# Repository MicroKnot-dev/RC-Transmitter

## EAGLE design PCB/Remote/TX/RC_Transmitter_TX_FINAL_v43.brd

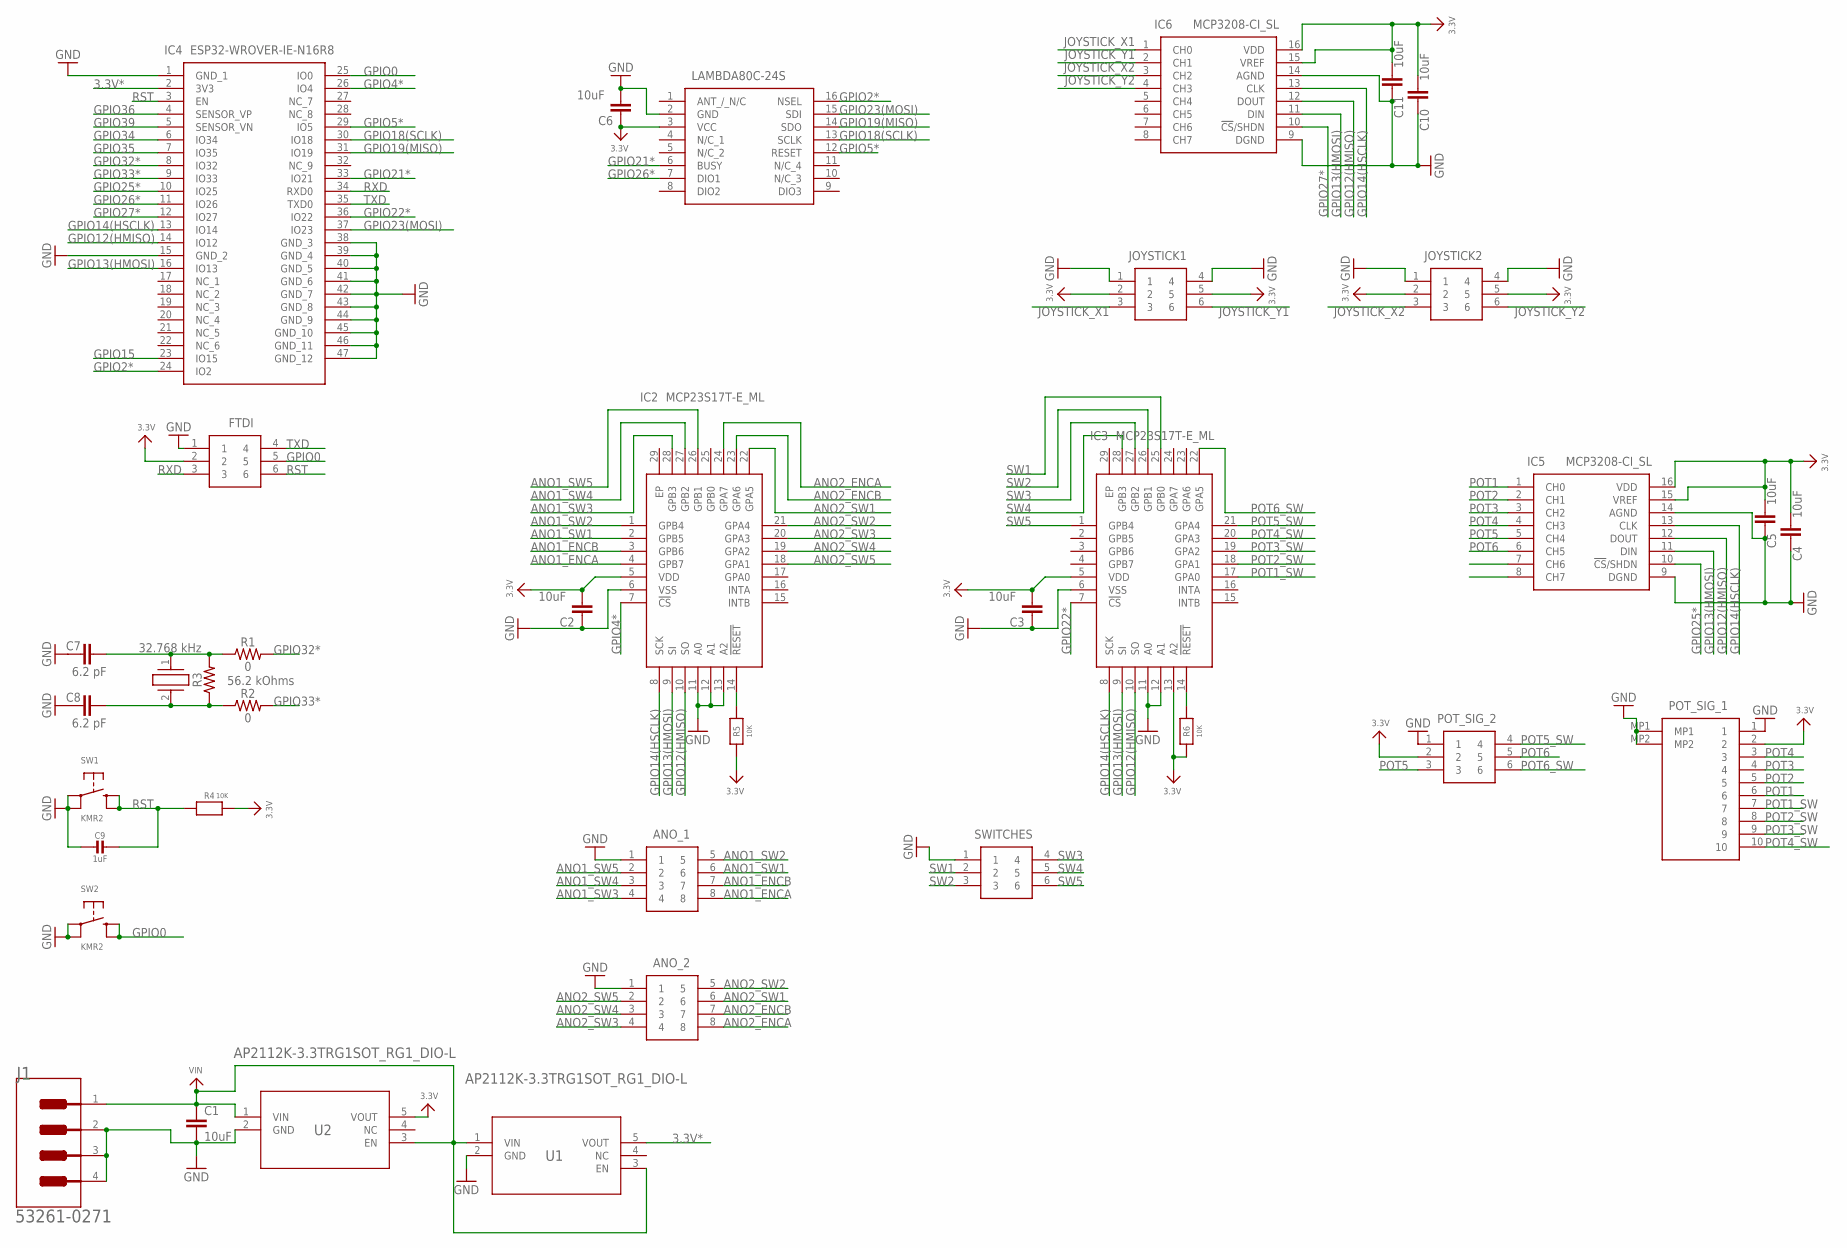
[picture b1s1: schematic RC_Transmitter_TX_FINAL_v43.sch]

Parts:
ANO_1, ANO_2: 0532610871; 53261-0871
C1, C2, C3, C4, C5, C6, C10, C11: 10uF; 0805
C7, C8: 6.2 pF; CAPC2012X110
C9: 1uF; 0805-NO
CRYSTAL: 32.768 kHz; ECX327CDX1293
FTDI: 0532610671
IC1: LAMBDA80C-24S; LAMBDA80C24S
IC2, IC3: MCP23S17T-E_ML; QFN65P600X600X100-29N
IC4: ESP32-WROVER-IE-N16R8; ESP32WROVERIEN16R8
IC5, IC6: MCP3208-CI_SL; SOIC127P600X175-16N
J1: MOLEX_53261-0271MOLEX_53261-0271_0_0; MOLEX_53261-0271_0
JOYSTICK1, JOYSTICK2: 0532610671
POT_SIG_1: 0532611071
POT_SIG_2: 0532610671
R1, R2: 0; 0603
R3: 56.2 kOhms; 0603
R4, R5, R6: 10K; _0805
SW1, SW2: KMR2; BTN_KMR2_4.6X2.8
SWITCHES: 0532610671
U1, U2: AP2112K-3.3TRG1SOT_RG1_DIO-L; SOT_RG1_DIO-L

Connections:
3.3V: C2.2, C3.2, C4.2, C5.2, C6.1, C10.2, C11.2, FTDI.2, IC1.3 (VCC), IC2.5 (VDD), IC3.5 (VDD), IC3.13 (A2), IC5.15 (VREF), IC5.16 (VDD), IC6.15 (VREF), IC6.16 (VDD), JOYSTICK1.2, JOYSTICK1.5, JOYSTICK2.2, JOYSTICK2.5, POT_SIG_1.2, POT_SIG_2.2, R4.2, R5.1, R6.1, U2.5 (VOUT)
3.3V*: IC4.2 (3V3), U1.5 (VOUT)
ANO1_ENCA: ANO_1.8, IC2.4 (GPB7)
ANO1_ENCB: ANO_1.7, IC2.3 (GPB6)
ANO1_SW1: ANO_1.6, IC2.2 (GPB5)
ANO1_SW2: ANO_1.5, IC2.1 (GPB4)
ANO1_SW3: ANO_1.4, IC2.28 (GPB3)
ANO1_SW4: ANO_1.3, IC2.27 (GPB2)
ANO1_SW5: ANO_1.2, IC2.26 (GPB1)
ANO2_ENCA: ANO_2.8, IC2.24 (GPA7)
ANO2_ENCB: ANO_2.7, IC2.23 (GPA6)
ANO2_SW1: ANO_2.6, IC2.22 (GPA5)
ANO2_SW2: ANO_2.5, IC2.21 (GPA4)
ANO2_SW3: ANO_2.4, IC2.20 (GPA3)
ANO2_SW4: ANO_2.3, IC2.19 (GPA2)
ANO2_SW5: ANO_2.2, IC2.18 (GPA1)
GND: ANO_1.1, ANO_2.1, C1.2, C2.1, C3.1, C4.1, C5.1, C6.2, C7.1, C8.1, C9.2, C10.1, C11.1, FTDI.1, IC1.2 (GND), IC2.6 (VSS), IC2.11 (A0), IC2.12 (A1), IC2.13 (A2), IC3.6 (VSS), IC3.11 (A0), IC3.12 (A1), IC4.1 (GND_1), IC4.15 (GND_2), IC4.38 (GND_3), IC4.39 (GND_4), IC4.40 (GND_5), IC4.41 (GND_6), IC4.42 (GND_7), IC4.43 (GND_8), IC4.44 (GND_9), IC4.45 (GND_10), IC4.46 (GND_11), IC4.47 (GND_12), IC5.9 (DGND), IC5.14 (AGND), IC6.9 (DGND), IC6.14 (AGND), J1.2, J1.3 (MNT_1), J1.4 (MNT_2), JOYSTICK1.1, JOYSTICK1.4, JOYSTICK2.1, JOYSTICK2.4, POT_SIG_1.1, POT_SIG_1.MP1, POT_SIG_1.MP2, POT_SIG_2.1, SW1.A, SW1.A' (P1), SW2.A, SW2.A' (P1), SWITCHES.1, U1.2 (GND), U2.2 (GND)
GPIO0: FTDI.5, IC4.25 (IO0), SW2.B (S), SW2.B' (S1)
GPIO2*: IC1.16 (NSEL), IC4.24 (IO2)
GPIO4*: IC2.7 (!CS), IC4.26 (IO4)
GPIO5*: IC1.12 (RESET), IC4.29 (IO5)
GPIO12(HMISO): IC2.10 (SO), IC3.10 (SO), IC4.14 (IO12), IC5.12 (DOUT), IC6.12 (DOUT)
GPIO13(HMOSI): IC2.9 (SI), IC3.9 (SI), IC4.16 (IO13), IC5.11 (DIN), IC6.11 (DIN)
GPIO14(HSCLK): IC2.8 (SCK), IC3.8 (SCK), IC4.13 (IO14), IC5.13 (CLK), IC6.13 (CLK)
GPIO15: IC4.23 (IO15)
GPIO18(SCLK): IC1.13 (SCLK), IC4.30 (IO18)
GPIO19(MISO): IC1.14 (SDO), IC4.31 (IO19)
GPIO21*: IC1.6 (BUSY), IC4.33 (IO21)
GPIO22*: IC3.7 (!CS), IC4.36 (IO22)
GPIO23(MOSI): IC1.15 (SDI), IC4.37 (IO23)
GPIO25*: IC4.10 (IO25), IC5.10 (!CS!/SHDN)
GPIO26*: IC1.7 (DIO1), IC4.11 (IO26)
GPIO27*: IC4.12 (IO27), IC6.10 (!CS!/SHDN)
GPIO32*: IC4.8 (IO32), R1.2
GPIO33*: IC4.9 (IO33), R2.2
GPIO34: IC4.6 (IO34)
GPIO35: IC4.7 (IO35)
GPIO36: IC4.4 (SENSOR_VP)
GPIO39: IC4.5 (SENSOR_VN)
JOYSTICK_X1: IC6.1 (CH0), JOYSTICK1.3
JOYSTICK_X2: IC6.3 (CH2), JOYSTICK2.3
JOYSTICK_Y1: IC6.2 (CH1), JOYSTICK1.6
JOYSTICK_Y2: IC6.4 (CH3), JOYSTICK2.6
unnamed: C7.2, CRYSTAL.1 (X1), R1.1, R3.2
unnamed: C8.2, CRYSTAL.2 (X2), R2.1, R3.1
unnamed: IC2.14 (!RESET), R5.2
unnamed: IC3.14 (!RESET), R6.2
POT1: IC5.1 (CH0), POT_SIG_1.6
POT1_SW: IC3.17 (GPA0), POT_SIG_1.7
POT2: IC5.2 (CH1), POT_SIG_1.5
POT2_SW: IC3.18 (GPA1), POT_SIG_1.8
POT3: IC5.3 (CH2), POT_SIG_1.4
POT3_SW: IC3.19 (GPA2), POT_SIG_1.9
POT4: IC5.4 (CH3), POT_SIG_1.3
POT4_SW: IC3.20 (GPA3), POT_SIG_1.10
POT5: IC5.5 (CH4), POT_SIG_2.3
POT5_SW: IC3.21 (GPA4), POT_SIG_2.4
POT6: IC5.6 (CH5), POT_SIG_2.5
POT6_SW: IC3.22 (GPA5), POT_SIG_2.6
RST: C9.1, FTDI.6, IC4.3 (EN), R4.1, SW1.B (S), SW1.B' (S1)
RXD: FTDI.3, IC4.34 (RXD0)
SW1: IC3.25 (GPB0), SWITCHES.2
SW2: IC3.26 (GPB1), SWITCHES.3
SW3: IC3.27 (GPB2), SWITCHES.4
SW4: IC3.28 (GPB3), SWITCHES.5
SW5: IC3.1 (GPB4), SWITCHES.6
TXD: FTDI.4, IC4.35 (TXD0)
VIN: C1.1, J1.1, U1.1 (VIN), U1.3 (EN), U2.1 (VIN), U2.3 (EN)

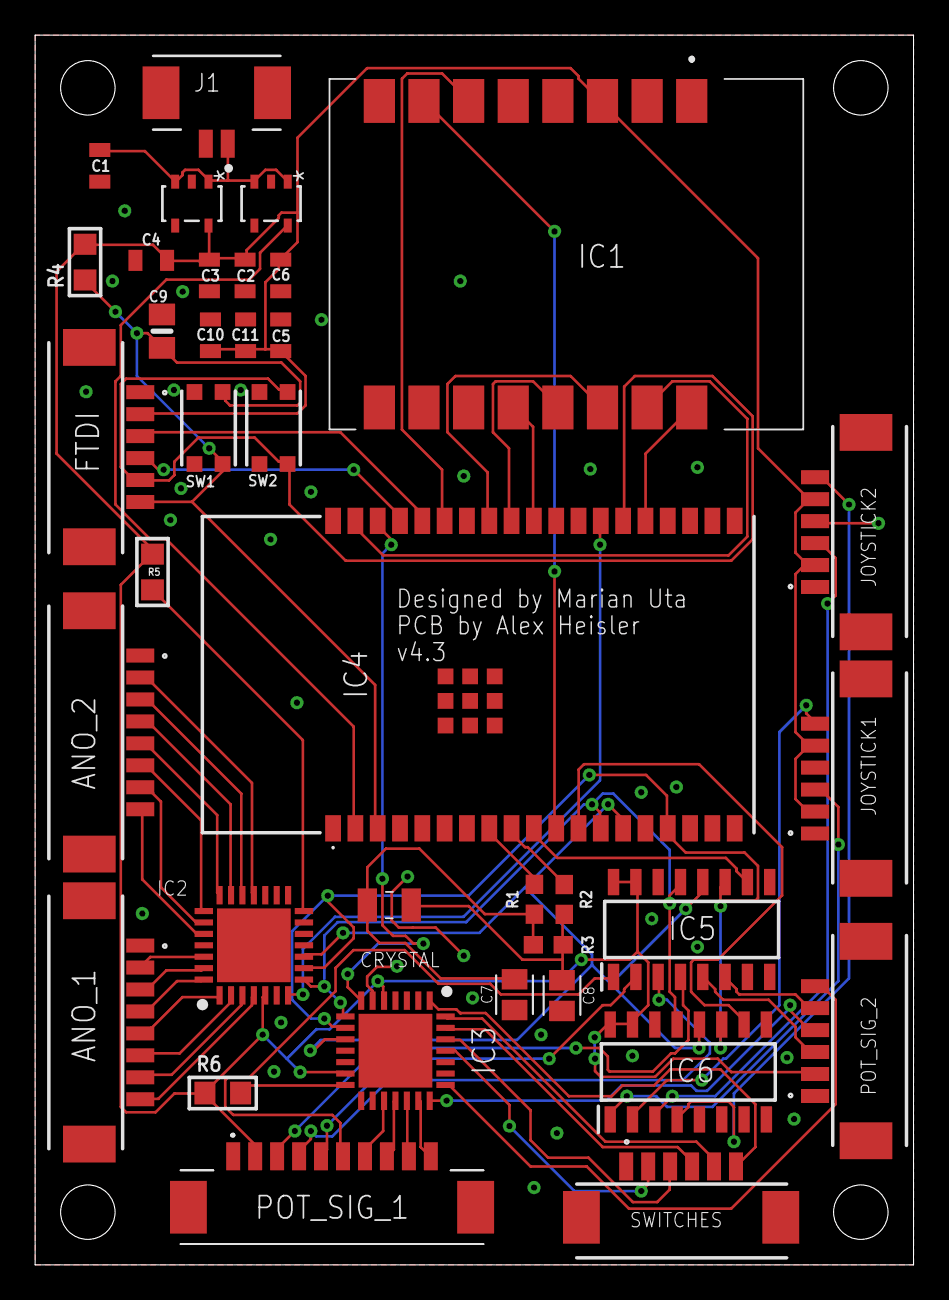
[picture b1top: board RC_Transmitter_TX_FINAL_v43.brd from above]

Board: 2 copper layers, 50.0 x 70.0 mm, 37 parts (0 on the bottom side), 63 nets.

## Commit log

2023-05-26 Step Files
2023-05-26 Directory Rename
2023-05-26 STL Files
2023-05-27 [Remote] PCB Files

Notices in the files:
parts and their libraries:
SparkFun-Capacitors: Licensing: Creative Commons ShareAlike 4.0 International - https://creativecommons.org/licenses/by-sa/4.0
microbuilder: This work is placed in the public domain, and may be freely used for commercial and non-commercial work with the following conditions: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
